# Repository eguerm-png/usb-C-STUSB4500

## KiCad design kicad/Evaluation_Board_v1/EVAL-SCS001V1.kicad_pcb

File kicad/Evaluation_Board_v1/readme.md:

## Evaluation Board for the STUSB4500

This is the evaluation board for the STUSB4500, based on the datasheet in /datasheets/DB_eval-scs001v1.pdf.

My main questions are as follows (sorry for lack of brevity)

1. I have included the test points in the datasheet schematic; do we want that?
2. The STUSB4500 symbol I’m using doesn't have a 0 pin to ground; is that fine?
3. The symbol for the USB-C connection is missing pins (like the 2nd BUS pin, it only has one) is that ok or should I find another one? From my research, it seems like it's alright.
4. As I understand it, for the USB-C connector symbol, the bottom and top connections to ground are the shield pin represented by the shield pin in the symbol I'm using. Is that correct?

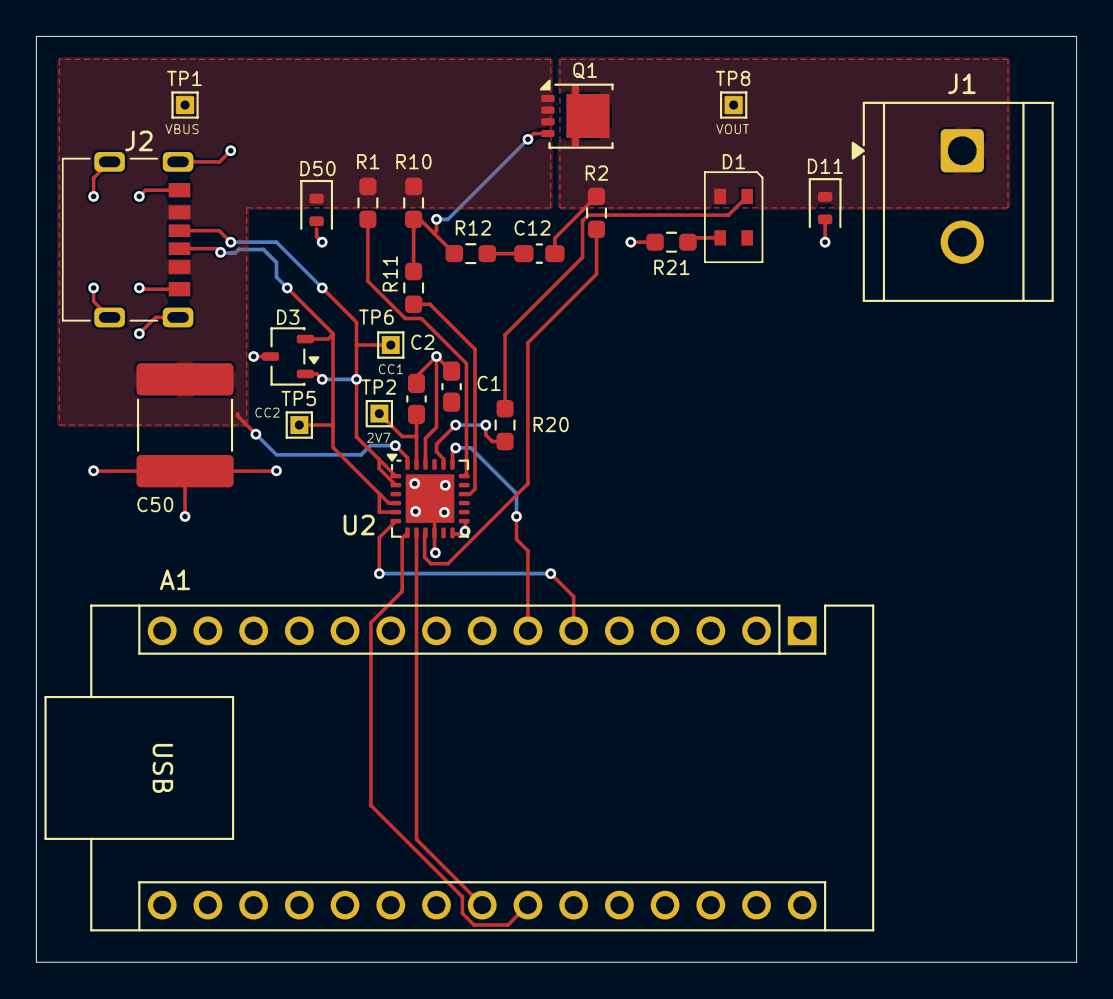
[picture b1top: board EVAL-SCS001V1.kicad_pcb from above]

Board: 2 copper layers, 57.8 x 51.4 mm, 25 parts (0 on the bottom side), 19 nets.

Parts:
A1: Arduino_Nano_v3.x; Arduino_Nano
C1, C2: 1uF; C_0603_1608Metric_Pad1.08x0.95mm_HandSolder
C12: 100nF; C_0603_1608Metric_Pad1.08x0.95mm_HandSolder
C50: 4.7uF; C_2220_5750Metric
D1: LTST-C19HE1WT?; LED_Avago_PLCC4_3.2x2.8mm_CW
D3: ESDA5V3L; SOT-23-3
D11, D50: ESDA25P35; D_SOD-323
J1: Screw_Terminal_01x02; TerminalBlock_CUI_TB007-508-02_1x02_P5.08mm_Horizontal
J2: USB_C_Receptacle_PowerOnly_6P; Amp_10164359_USB_Power
Q1: STL6P3LLH6; VSON-8_3.3x3.3mm_P0.65mm_NexFET
R1, R2: 1k; R_0603_1608Metric_Pad0.98x0.95mm_HandSolder
R10: 100k; R_0603_1608Metric_Pad0.98x0.95mm_HandSolder
R11, R20, R21: 22k; R_0603_1608Metric_Pad0.98x0.95mm_HandSolder
R12: 100R; R_0603_1608Metric_Pad0.98x0.95mm_HandSolder
TP1, TP2, TP5, TP6, TP8: TestPoint_Small; TestPoint_THTPad_1.0x1.0mm_Drill0.5mm
U2: STUSB4500QTR; QFN-24-1EP_4x4mm_P0.5mm_EP2.7x2.7mm

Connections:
/CC1 Test: D3.1 (K), J2.A5 (CC1), TP6.1 (1_1), U2.1 (CC1DB), U2.2 (CC1)
/VBUS: C50.1, D50.1 (K), J2.A9 (VBUS), J2.B9 (VBUS), Q1.1 (S), Q1.2 (S), Q1.3 (S), R1.1, R10.1, TP1.1 (1_1), U2.24 (VDD)
/VOUT: C12.1, D1.4 (A), D11.1 (K), J1.1, Q1.5 (D), R2.1, TP8.1 (1_1)
GND: A1.4 (GND), A1.29 (GND), C1.1, C2.1, C50.2, D3.3 (A), D11.2 (A), D50.2 (A), J1.2, J2.A12 (GND), J2.B12 (GND), J2.S1 (SHIELD), R21.2, U2.10 (GND), U2.12 (ADDR0), U2.13 (ADDR1), U2.22 (VSYS), U2.25 (GND)
unnamed: A1.23 (A4), U2.8 (SDA)
unnamed: A1.24 (A5), U2.7 (SCL)
unnamed: A1.6 (D3), U2.6 (RESET)
unnamed: A1.7 (D4), U2.19 (ALERT)
unnamed: C12.2, R12.2
unnamed: D1.3 (BK), R21.1
unnamed: D1.1 (RK), R20.1
unnamed: D3.2 (K), J2.B5 (CC2), TP5.1 (1_1), U2.4 (CC2), U2.5 (CC2DB)
unnamed: Q1.4 (G), R10.2, R11.1, R12.1
unnamed: R2.2, U2.9 (DISCH)
unnamed: R20.2, U2.20 (POWER_OK2)
unnamed: R11.2, U2.16 (VBUS_EN_SNK)
unnamed: R1.2, U2.18 (VBUS_VS_DISCH)
unnamed: C1.2, U2.21 (VREG_1V2)
unnamed: C2.2, TP2.1 (1_1), U2.23 (VREG_2V7)
